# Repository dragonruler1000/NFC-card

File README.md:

# NFC card
All this is is a NTAG 211, a warm white led, a cap, and a resister. the hardest part was figuring out how to make the antenna because i couldn't find a exsisting footprint for one like exsists for easyeda.

I have wanted to play around with NFC stuff for a while but just haven't got around to buying any NFC cards or pucks and i though i've been invited to share The Book of Mormon so i might as well make a custom NFC card to make sharing it easier.

To use this project all you need to do is order it as a PCBA (unless you want to hand solder smd componets) using the components listed in the BOM. Then when it arrives you can use it like any NFC card. so program it via NFC tools or another NFC programming app and use a nfc enabled phone to read the nfc card.

## Images

3d model front

3D model back

# BOM:

| Item Count | Item Name        | Unit Price | Total Price | Price with discount | Link                                                             | Running Total | Running Total with discounts | lcsc/jlcpcb part number | customer part number | Notes                                                |
|------------|------------------|------------|-------------|---------------------|------------------------------------------------------------------|---------------|------------------------------|-------------------------|----------------------|------------------------------------------------------|
| 20         | Warm white LED   | 0.0135     | 0.27        | 0.27                | https://jlcpcb.com/partdetail/XINGLIGHT-XL2012WWC/C965820        | 0.29          | 0.29                         | C965820                 | 1                    |                                                      |
| 20         | 47Ω resistor     | 0.0004     | 0.01        | 0.01                | https://jlcpcb.com/partdetail/GiantOhm-GR0402J47RTAG00/C49653152 | 0.3           | 0.3                          | C49653152               | 2                    | love how cheap smd parts are from jlcbcp for pcba    |
| 5          | NTAG I²C plus 1K | 0.08015    | 0.4         | 0.4                 | https://jlcpcb.com/partdetail/NXPSemicon-NT3H2111W0FTTJ/C2654884 | 0.72          | 0.72                         | C2654884                | 3                    |                                                      |
| 5          | 220nF capaciter  | 0.0016     | 0.01        | 0.01                | https://jlcpcb.com/partdetail/HRE-CGA0402X5R224K100GT/C7503518   | 0.73          | 0.73                         | C49653152               | 4                    |                                                      |
| 1          | PCBA             | 27.9       | 27.9        | 18.9                |                                                                  | 30.3          | 20.76                        |                         | 5                    | i have a $9 smt coupon that i can use after the 23rd |
| 1          | pcb              | 3.3        | 3.3         | 3.3                 | jlcpcb.com                                                       | 33.8          | 24.26                        |                         | 6                    |                                                      |
| 1          | Shipping         | 11.8       | 11.8        | 11.8                | jlcpcb.com                                                       | 46.31         | 36.77                        |                         |                      |                                                      |

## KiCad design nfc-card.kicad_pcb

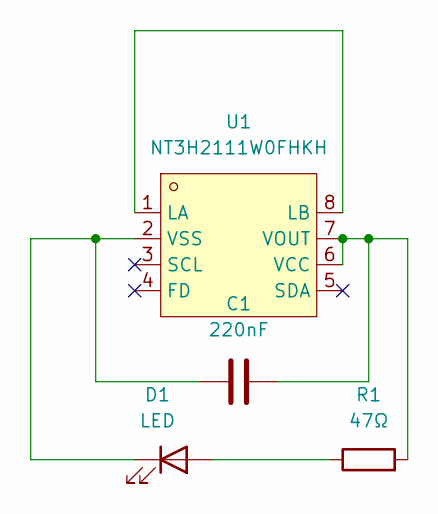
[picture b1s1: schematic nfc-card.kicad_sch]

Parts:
C1: 220nF; C_0402_1005Metric_Pad0.74x0.62mm_HandSolder
D1: LED; LED_0805_2012Metric_Pad1.15x1.40mm_HandSolder
R1: 47Ω; R_0402_1005Metric_Pad0.72x0.64mm_HandSolder
U1: NT3H2111W0FHKH; XQFN-8_L1.6-W1.6-P0.50-BL_NT3H2111W0FHKH; LCSC Part C710403

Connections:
unnamed: D1.2 (A), R1.1
unnamed: C1.1, D1.1 (K), U1.2 (VSS)
unnamed: U1.1 (LA), U1.8 (LB)
unnamed: C1.2, R1.2, U1.6 (VCC), U1.7 (VOUT)

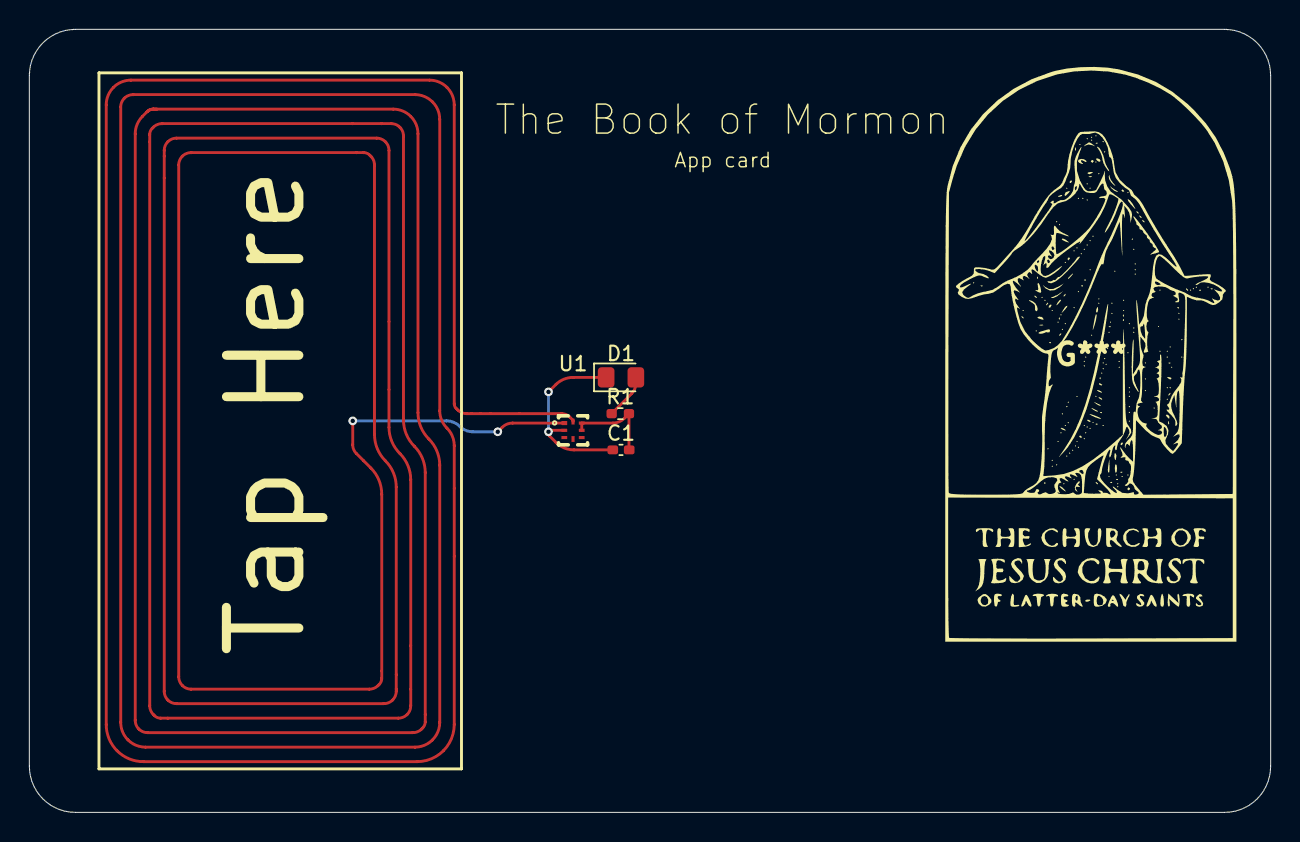
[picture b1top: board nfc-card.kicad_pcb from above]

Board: 2 copper layers, 85.6 x 54.0 mm, 4 parts (0 on the bottom side), 4 nets.

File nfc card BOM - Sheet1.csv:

Item Count,Item Name,Unit Price,Total Price,Price with discount,Link,Running Total,Running Total with discounts,lcsc/jlcpcb part number,customer part number,Notes
5,Warm white LED,0.0135,0.07,0.07,https://jlcpcb.com/partdetail/XINGLIGHT-XL2012WWC/C965820,0.07,0.07,C965820,1,
5,47Ω resistor,0.0004,0,0,https://jlcpcb.com/partdetail/GiantOhm-GR0402J47RTAG00/C49653152,0.07,0,C49653152,2,love how cheap smd parts are from jlcbcp for pcba
5,NTAG I²C plus 1K,0.08015,0.4,0.4,https://jlcpcb.com/partdetail/NXPSemicon-NT3H2111W0FHKH/C710403,0.49,0.42,C710403,3,
5,220nF capaciter,0.0016,0.01,0.01,https://jlcpcb.com/partdetail/HRE-CGA0402X5R224K100GT/C7503518,0.5,0.01,C49653152,4,
5,,,0,0,,0.5,0,,5,
1,,,0,0,,0.5,0,,6,

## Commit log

2026-02-16 starting to make nfc card project files
2026-02-16 made the schematic
2026-02-16 add screenshots folder to the repo
2026-02-16 Add CERN Open Hardware Licence Version 2
    Added the CERN Open Hardware Licence Version 2 - Permissive to the project.
2026-02-17 finnished silkscreen art and started on README
2026-02-17 finnished readme and set up production files for jlcpcb
2026-02-18 moving pcb stuff to pcb folder and update readme
2026-02-18 Fix image links in README.md
    Updated image links in README for better formatting and clarity.
2026-02-18 renamed images
2026-02-18 add README again
2026-02-18 fix images in readme
2026-02-18 Fix image paths in README.md
    Updated image paths in README to use screenshots directory.
2026-02-18 add more usage info to readme
2026-03-08 copied the BOM to the main directory
